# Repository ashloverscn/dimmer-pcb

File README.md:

# dimmer-pcb
dimmer-pcb

library: 

https://github.com/ashloverscn/atmega328-16mhz-ac-phase-control

https://github.com/ashloverscn/atmega8-16mhz-ac-phase-control

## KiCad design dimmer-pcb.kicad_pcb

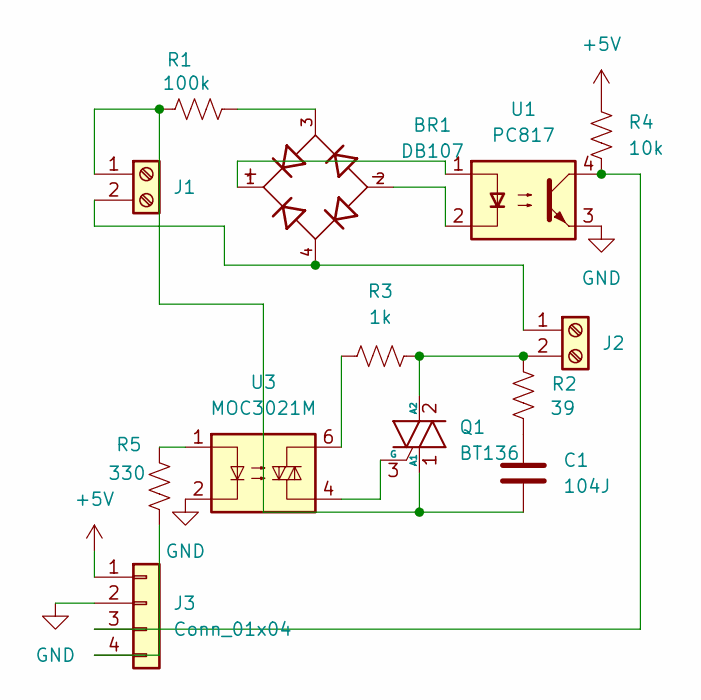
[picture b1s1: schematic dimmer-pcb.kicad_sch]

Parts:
BR1: DB107; DIP825W50P509L880H320Q4; PARTREV 13
C1: 104J; C_Rect_L18.0mm_W6.0mm_P15.00mm_FKS3_FKP3
J1, J2: TerminalBlock_MaiXu_MX126-5.0-02P_1x02_P5.00mm
J3: Conn_01x04; PinHeader_1x04_P2.54mm_Vertical
Q1: BT136; TO-220-3_Vertical
R1: 100k; R_Axial_DIN0207_L6.3mm_D2.5mm_P5.08mm_Vertical
R2: 39; R_Axial_DIN0207_L6.3mm_D2.5mm_P5.08mm_Vertical
R3: 1k; R_Axial_DIN0207_L6.3mm_D2.5mm_P2.54mm_Vertical
R4: 10k; R_Axial_DIN0207_L6.3mm_D2.5mm_P2.54mm_Vertical
R5: 330; R_Axial_DIN0207_L6.3mm_D2.5mm_P2.54mm_Vertical
U1: PC817; DIP-4_W7.62mm_LongPads
U3: MOC3021M; DIP-6_W7.62mm_LongPads

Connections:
+5V: J3.1, R4.1
GND: J3.2, U1.3, U3.2
unnamed: BR1.1, U1.1
unnamed: BR1.2, U1.2
unnamed: BR1.3, R1.2
unnamed: C1.1, R2.2
unnamed: C1.2, J1.1, Q1.1 (A1), R1.1
unnamed: BR1.4, J1.2, J2.1
unnamed: J2.2, Q1.2 (A2), R2.1, R3.1
unnamed: J3.3, R4.2, U1.4
unnamed: J3.4, R5.2
unnamed: Q1.3 (G), U3.4
unnamed: R3.2, U3.6
unnamed: R5.1, U3.1

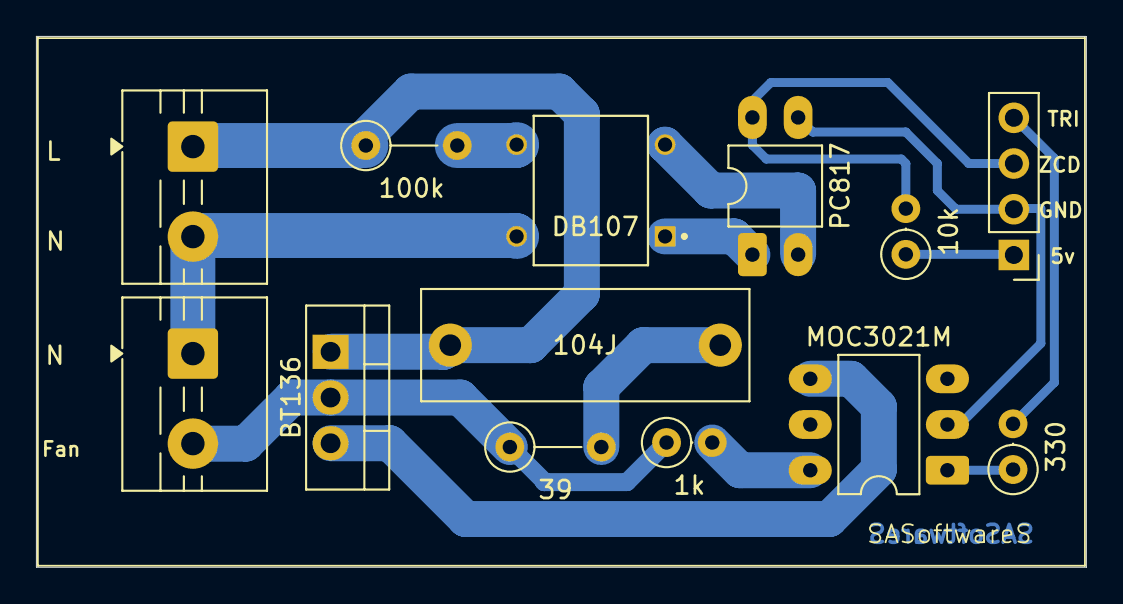
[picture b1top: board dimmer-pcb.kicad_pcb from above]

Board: 2 copper layers, 58.3 x 29.5 mm, 13 parts (0 on the bottom side), 14 nets.
